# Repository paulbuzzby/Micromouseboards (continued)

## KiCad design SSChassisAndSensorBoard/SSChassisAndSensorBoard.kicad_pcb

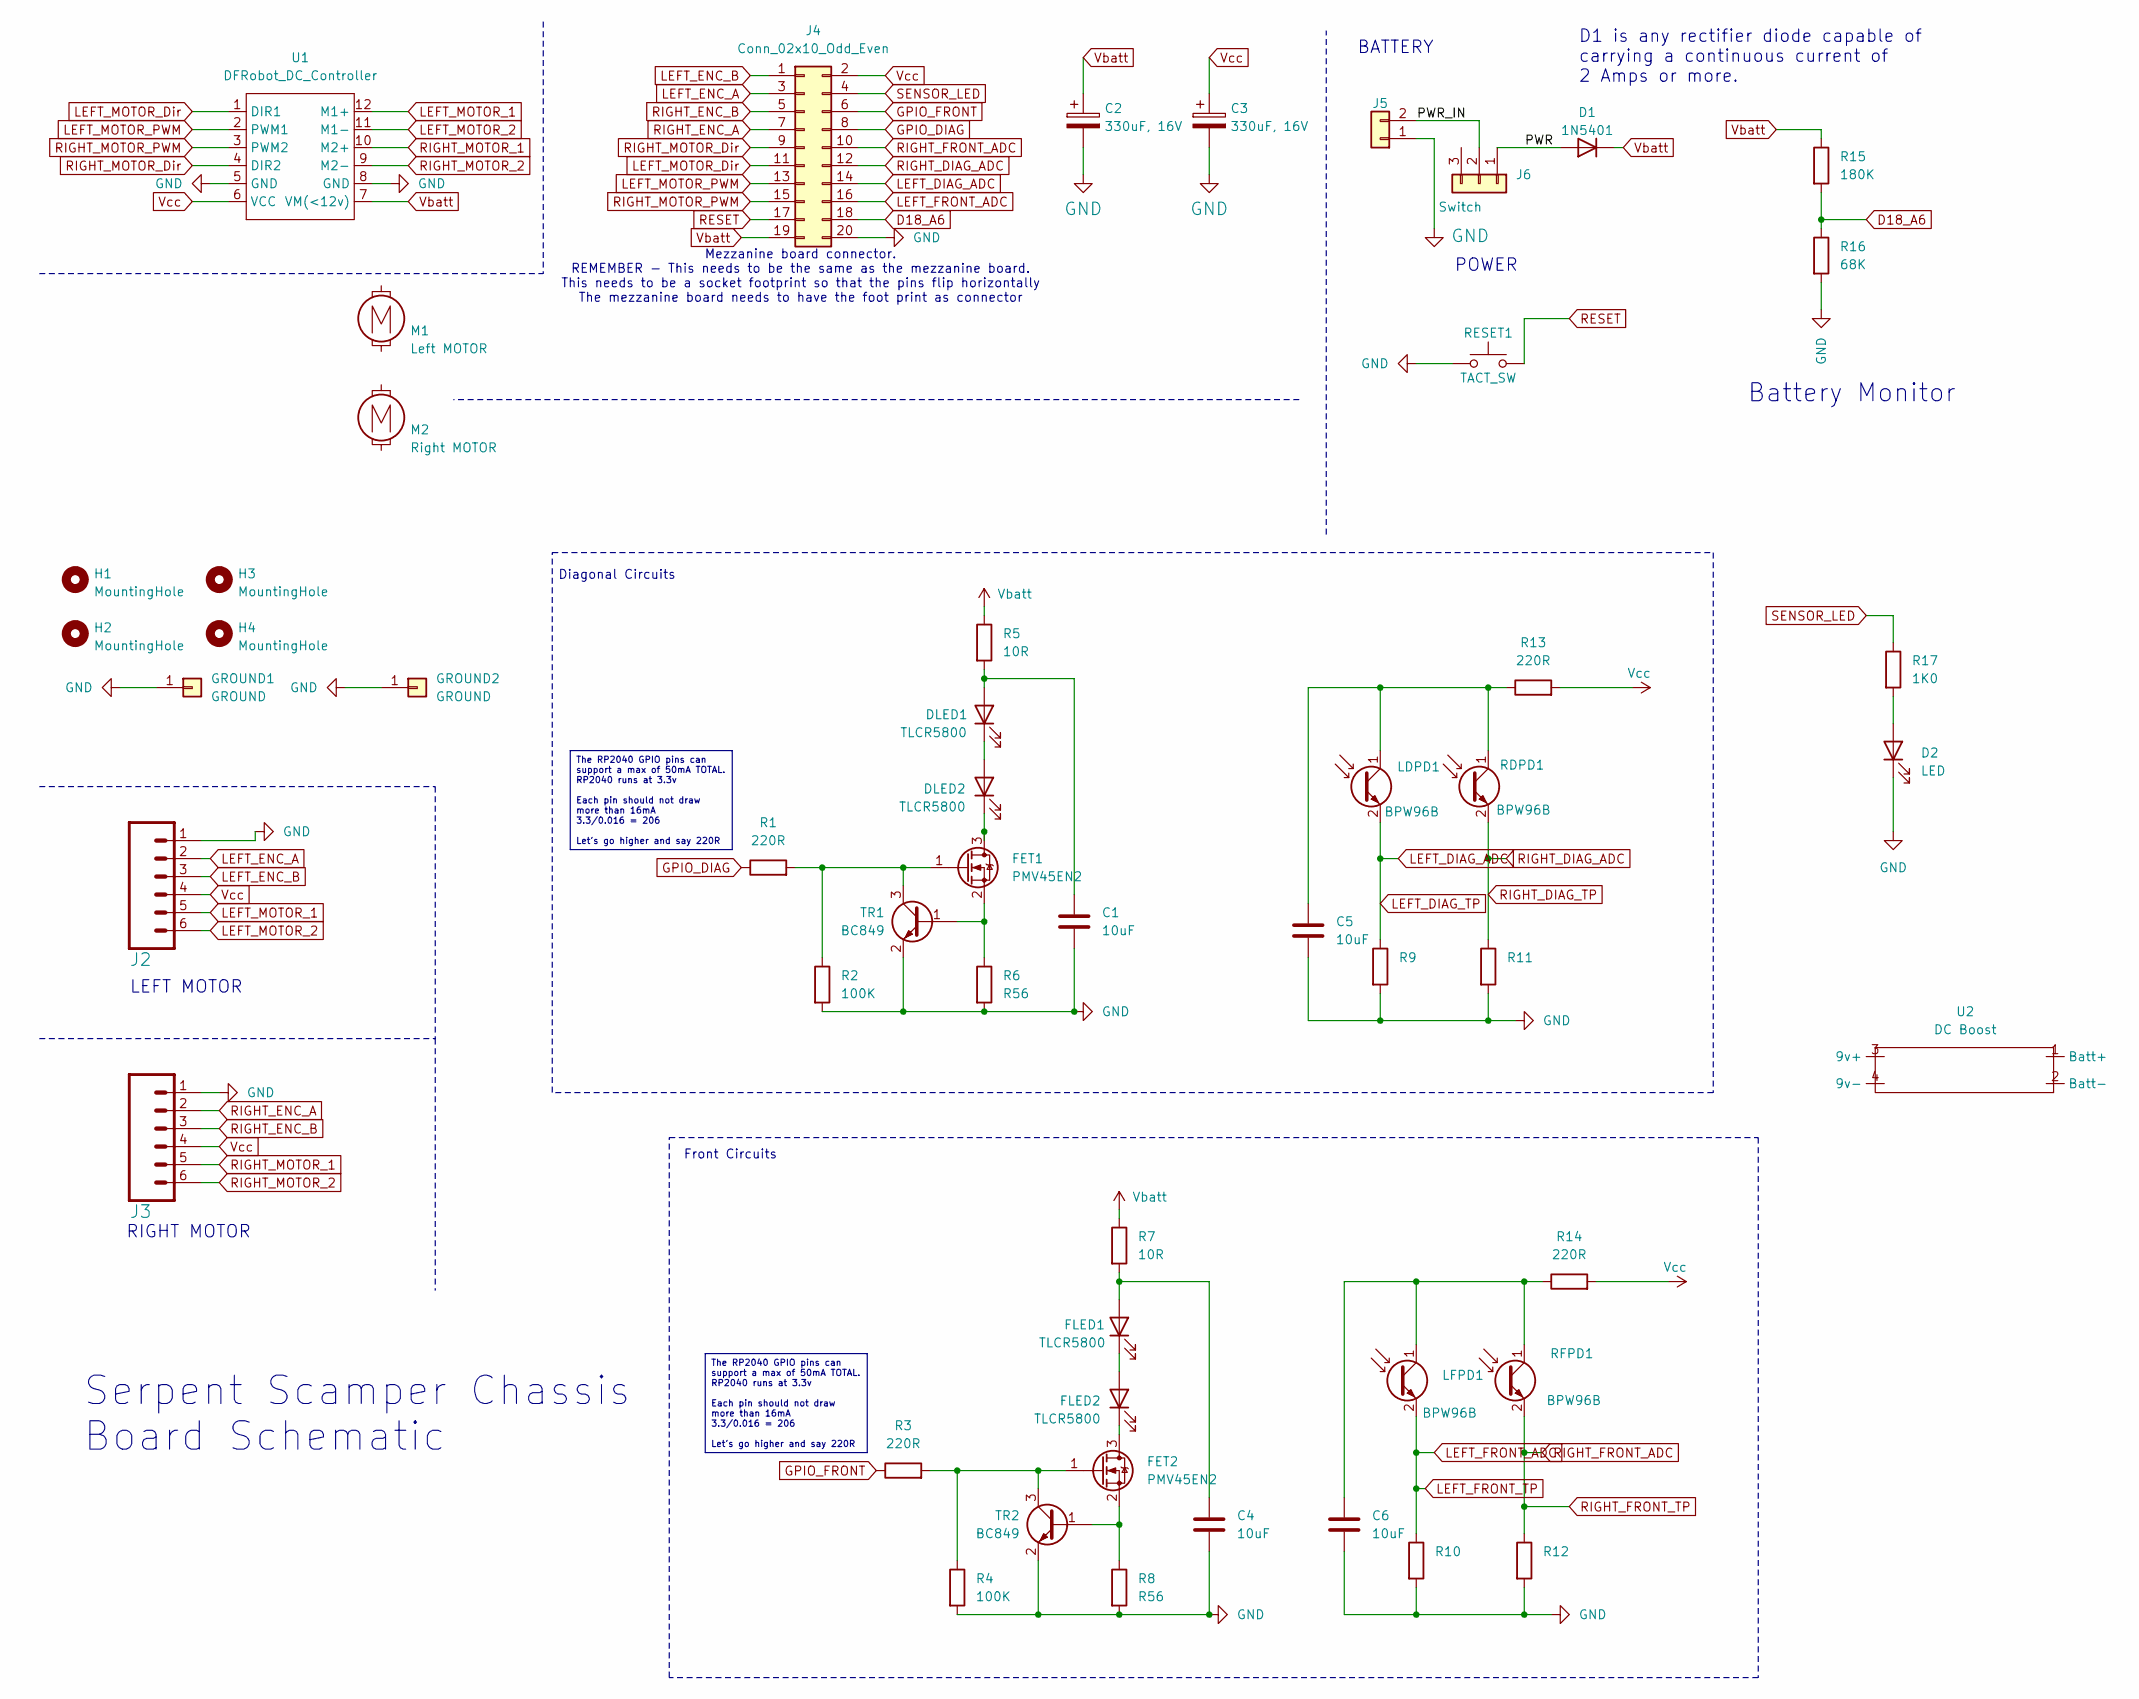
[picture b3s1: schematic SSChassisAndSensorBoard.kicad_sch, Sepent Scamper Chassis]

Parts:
C1, C4, C5, C6: 10uF; C_0805_2012Metric_Pad1.18x1.45mm_HandSolder
C2, C3: 330uF, 16V; CP_Radial_D8.0mm_P2.50mm
D1: 1N5401; D_DO-201AD_P15.24mm_Horizontal
D2: LED; LED_1206_3216Metric_Pad1.42x1.75mm_HandSolder
DLED1, DLED2: TLCR5800; LED_D5.0mm_Horizontal_O1.27mm_Z3.0mm
FET1, FET2: PMV45EN2; SOT-23_Handsoldering
FLED1, FLED2: TLCR5800; LED_D5.0mm_Horizontal_O1.27mm_Z3.0mm
GROUND1, GROUND2: GROUND; PinHeader_1x01_P2.54mm_Vertical
H1, H2, H3, H4: MountingHole; MountingHole_3.2mm_M3_clearance
J2, J3: CONN_06SILK_FEMALE_PTH; 1X06_LOCK_LONGPADS
J4: Conn_02x10_Odd_Even; PinSocket_2x10_P2.54mm_Vertical
J5: POWER; Molex_KK-254_AE-6410-02A_1x02_P2.54mm_Vertical
J6: Switch; PinHeader_1x03_P2.54mm_Vertical
LDPD1: BPW96B; LED_D5.0mm_Horizontal_O1.27mm_Z3.0mm
LFPD1: BPW96B; LED_D5.0mm_Horizontal_O1.27mm_Z3.0mm
M1: Left MOTOR; MINI-METAL-GEARMOTOR-WITH-BRACKET_Alt
M2: Right MOTOR; MINI-METAL-GEARMOTOR-WITH-BRACKET
R1, R3, R13, R14: 220R; R_0805_2012Metric_Pad1.20x1.40mm_HandSolder
R2, R4: 100K; R_0805_2012Metric_Pad1.20x1.40mm_HandSolder
R5, R7: 10R; R_0805_2012Metric_Pad1.20x1.40mm_HandSolder
R6, R8: R56; R_0805_2012Metric_Pad1.20x1.40mm_HandSolder
R9, R10, R11, R12: R; R_0805_2012Metric_Pad1.20x1.40mm_HandSolder
R15: 180K; R_Axial_DIN0207_L6.3mm_D2.5mm_P7.62mm_Horizontal
R16: 68K; R_Axial_DIN0207_L6.3mm_D2.5mm_P7.62mm_Horizontal
R17: 1K0; R_0805_2012Metric_Pad1.20x1.40mm_HandSolder
RDPD1: BPW96B; LED_D5.0mm_Horizontal_O1.27mm_Z3.0mm
RESET1: TACT_SW; SW_PUSH_6mm
RFPD1: BPW96B; LED_D5.0mm_Horizontal_O1.27mm_Z3.0mm
TR1, TR2: BC849; SOT-23_Handsoldering
U1: DFRobot_DC_Controller
U2: DC Boost

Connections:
/PWR: D1.2 (A), J6.1
/PWR_IN: J5.2, J6.2
D18_A6: J4.18, R15.2, R16.1
GND: C1.2, C2.2, C3.2, C4.2, C5.2, C6.2, D2.1 (K), GROUND1.1, GROUND2.1, J2.1, J3.1, J4.20, J5.1, R2.2, R4.2, R6.2, R8.2, R9.2, R10.2, R11.2, R12.2, R16.2, RESET1.1 (A), TR1.2 (E), TR2.2 (E), U1.5 (GND), U1.8 (GND)
GPIO_DIAG: J4.8, R1.1
GPIO_FRONT: J4.6, R3.1
LEFT_DIAG_ADC: J4.14, LDPD1.2 (E), R9.1
LEFT_ENC_A: J2.2, J4.3
LEFT_ENC_B: J2.3, J4.1
LEFT_FRONT_ADC: J4.16, LFPD1.2 (E), R10.1
LEFT_MOTOR_1: J2.5, U1.12 (M1+)
LEFT_MOTOR_2: J2.6, U1.11 (M1-)
LEFT_MOTOR_Dir: J4.11, U1.1 (DIR1)
LEFT_MOTOR_PWM: J4.13, U1.2 (PWM1)
unnamed: D2.2 (A), R17.2
unnamed: C1.1, DLED1.2 (A), R5.2
unnamed: DLED1.1 (K), DLED2.2 (A)
unnamed: DLED2.1 (K), FET1.3 (D)
unnamed: FET1.1 (G), R1.2, R2.1, TR1.3 (C)
unnamed: FET1.2 (S), R6.1, TR1.1 (B)
unnamed: FET2.3 (D), FLED2.1 (K)
unnamed: FET2.1 (G), R3.2, R4.1, TR2.3 (C)
unnamed: FET2.2 (S), R8.1, TR2.1 (B)
unnamed: C4.1, FLED1.2 (A), R7.2
unnamed: FLED1.1 (K), FLED2.2 (A)
unnamed: C5.1, LDPD1.1 (C), R13.1, RDPD1.1 (C)
unnamed: C6.1, LFPD1.1 (C), R14.1, RFPD1.1 (C)
RESET: J4.17, RESET1.2 (B)
RIGHT_DIAG_ADC: J4.12, R11.1, RDPD1.2 (E)
RIGHT_ENC_A: J3.2, J4.7
RIGHT_ENC_B: J3.3, J4.5
RIGHT_FRONT_ADC: J4.10, R12.1, RFPD1.2 (E)
RIGHT_MOTOR_1: J3.5, U1.10 (M2+)
RIGHT_MOTOR_2: J3.6, U1.9 (M2-)
RIGHT_MOTOR_Dir: J4.9, U1.4 (DIR2)
RIGHT_MOTOR_PWM: J4.15, U1.3 (PWM2)
SENSOR_LED: J4.4, R17.1
Vbatt: C2.1, D1.1 (K), J4.19, R5.1, R7.1, R15.1, U1.7 (VM(<12v))
Vcc: C3.1, J2.4, J3.4, J4.2, R13.2, R14.2, U1.6 (VCC)

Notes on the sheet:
The RP2040 GPIO pins can support a max of 50mA TOTAL. RP2040 runs at 3.3v Each pin should not draw more than 16mA 3.3/0.016 = 206 Let's go higher and say 220R
D1 is any rectifier diode capable of carrying a continuous current of 2 Amps or more.
Front Circuits
POWER
Diagonal Circuits
RIGHT MOTOR
BATTERY
Mezzanine board connector. REMEMBER - This needs to be the same as the mezzanine board. This needs to be a socket footprint so that the pins flip horizontally The mezzanine board needs to have the foot print as connector
Serpent Scamper Chassis Board Schematic
LEFT MOTOR
Battery Monitor

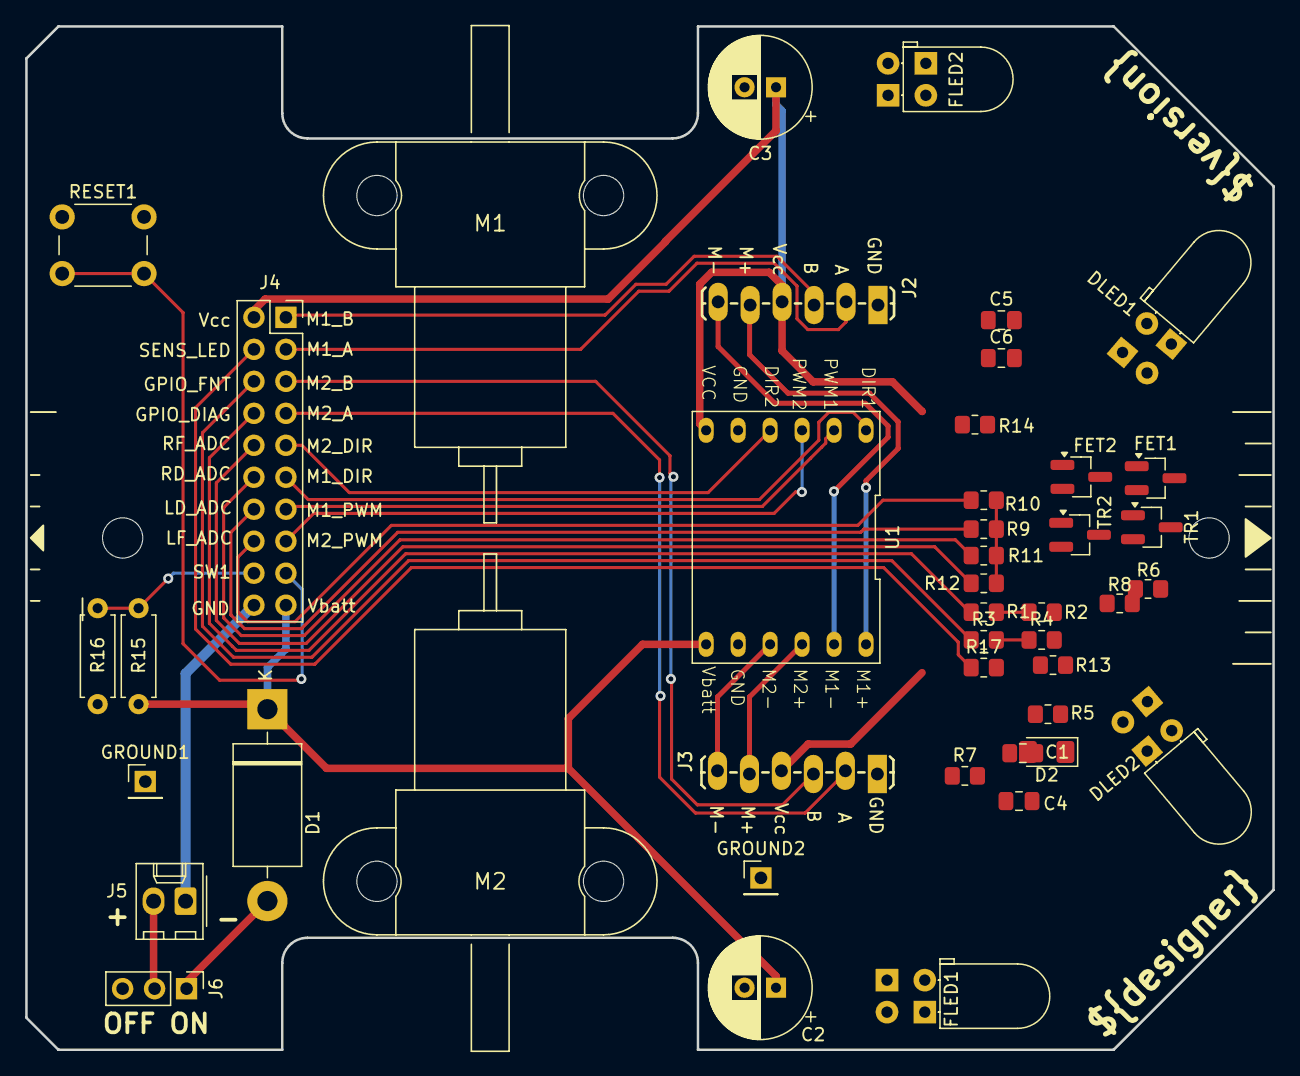
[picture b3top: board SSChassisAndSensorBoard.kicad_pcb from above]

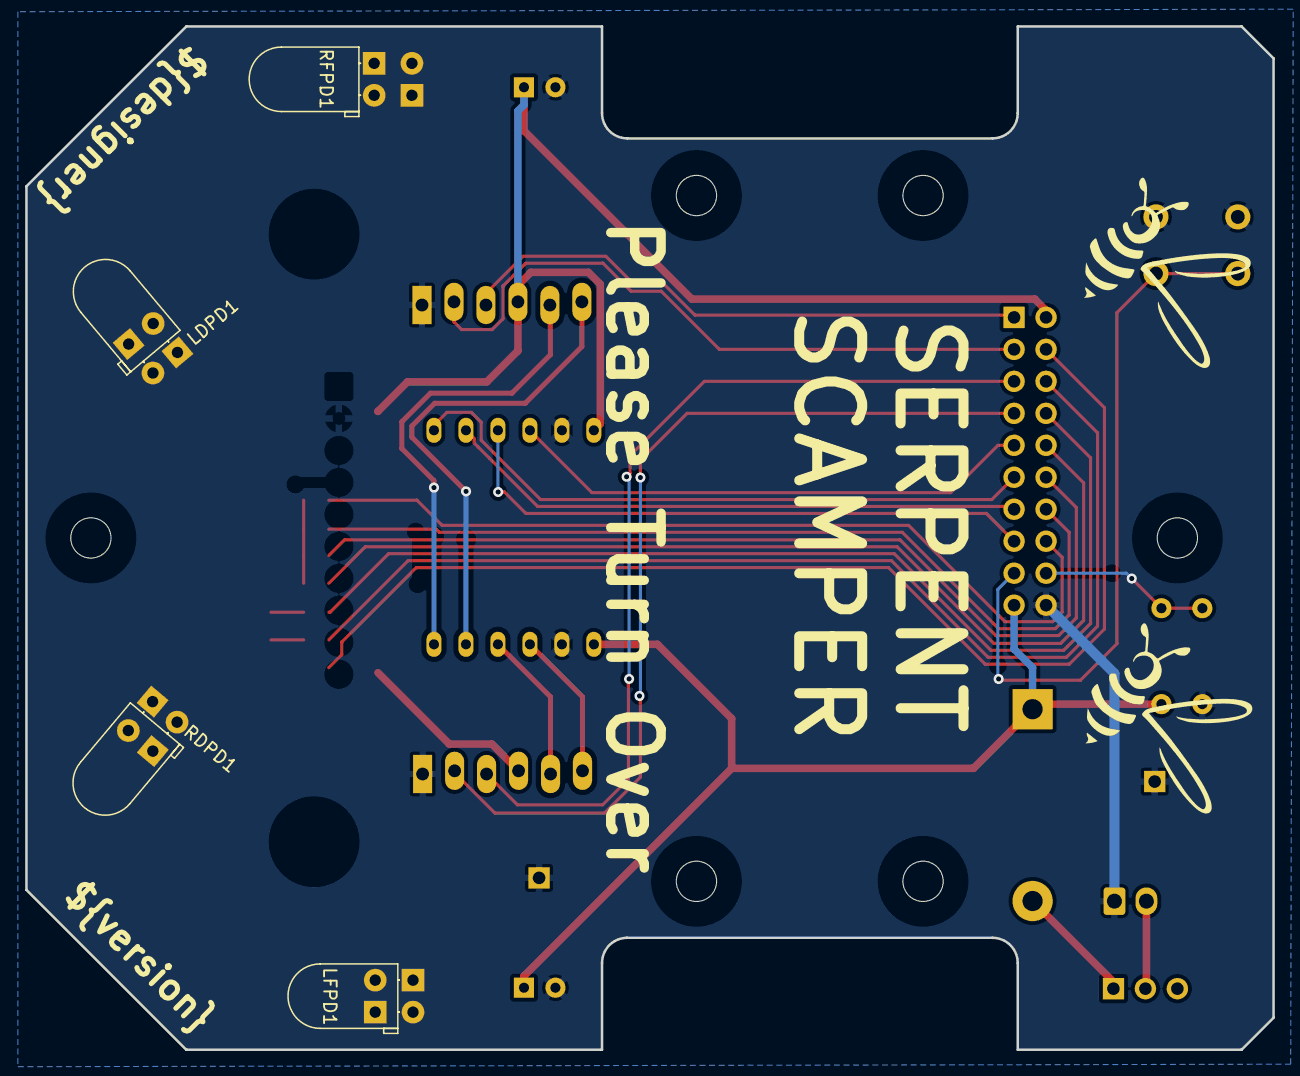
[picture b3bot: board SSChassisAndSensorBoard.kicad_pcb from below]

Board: 2 copper layers, 99.1 x 81.3 mm, 52 parts (4 on the bottom side), 39 nets.

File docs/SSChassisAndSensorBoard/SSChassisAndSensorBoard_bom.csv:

Reference,Value,Qty,Note,Description
C1 C4 C5 C6,10uF,4,,Unpolarized capacitor
C2 C3,"330uF, 16V",2,Maximum height is 10mm,
D1,1N5401,1,> 2A rectifier. Shottky is good,
D2,LED,1,,Light emitting diode
DLED1 DLED2 FLED1 FLED2,TLCR5800,4,,Light emitting diode
FET1 FET2,PMV45EN2,2,,"N-Channel MOSFET, 5.1 A, 30 V, 3-Pin SOT-23"
GROUND1 GROUND2 J4 J5 J6,GROUND,5,"0.1"" pitch, polarised, any type","Generic connector, single row, 01x01, script generated (kicad-library-utils/schlib/autogen/connector/) Generic connector, double row, 02x10, odd/even pin numbering scheme (row 1 odd numbers, row 2 even numbers), script generated (kicad-library-utils/schlib/autogen/connector/) Generic connector, single row, 01x03, script generated (kicad-library-utils/schlib/autogen/connector/)"
J2 J3,CONN_06SILK_FEMALE_PTH,2,"6 pin header, 0.1"", male",
LDPD1 LFPD1 RDPD1 RFPD1,BPW96B,4,,Photodiode
M1,Left MOTOR,1,commercial mounts need bushing for screws,
M2,Right MOTOR,1,commercial mounts need bushing for screws,
R2 R4,100K,2,,Resistor
R5 R7,10R,2,,Resistor
R15,180K,1,,Resistor
R17,1K0,1,,Resistor
R1 R3 R13 R14,220R,4,,Resistor
R16,68K,1,,Resistor
R9 R10 R11 R12,R,4,,Resistor
R6 R8,R56,2,,Resistor
RESET1,TACT_SW,1,,TACT switch 6mm 4.5mm
TR1 TR2,BC849,2,,"0.1A Ic, 30V Vce, NPN Transistor, SOT-23"
U2,DC Boost,1,,DC-DC boost converter
U1,DFRobot_DC_Controller,1,,

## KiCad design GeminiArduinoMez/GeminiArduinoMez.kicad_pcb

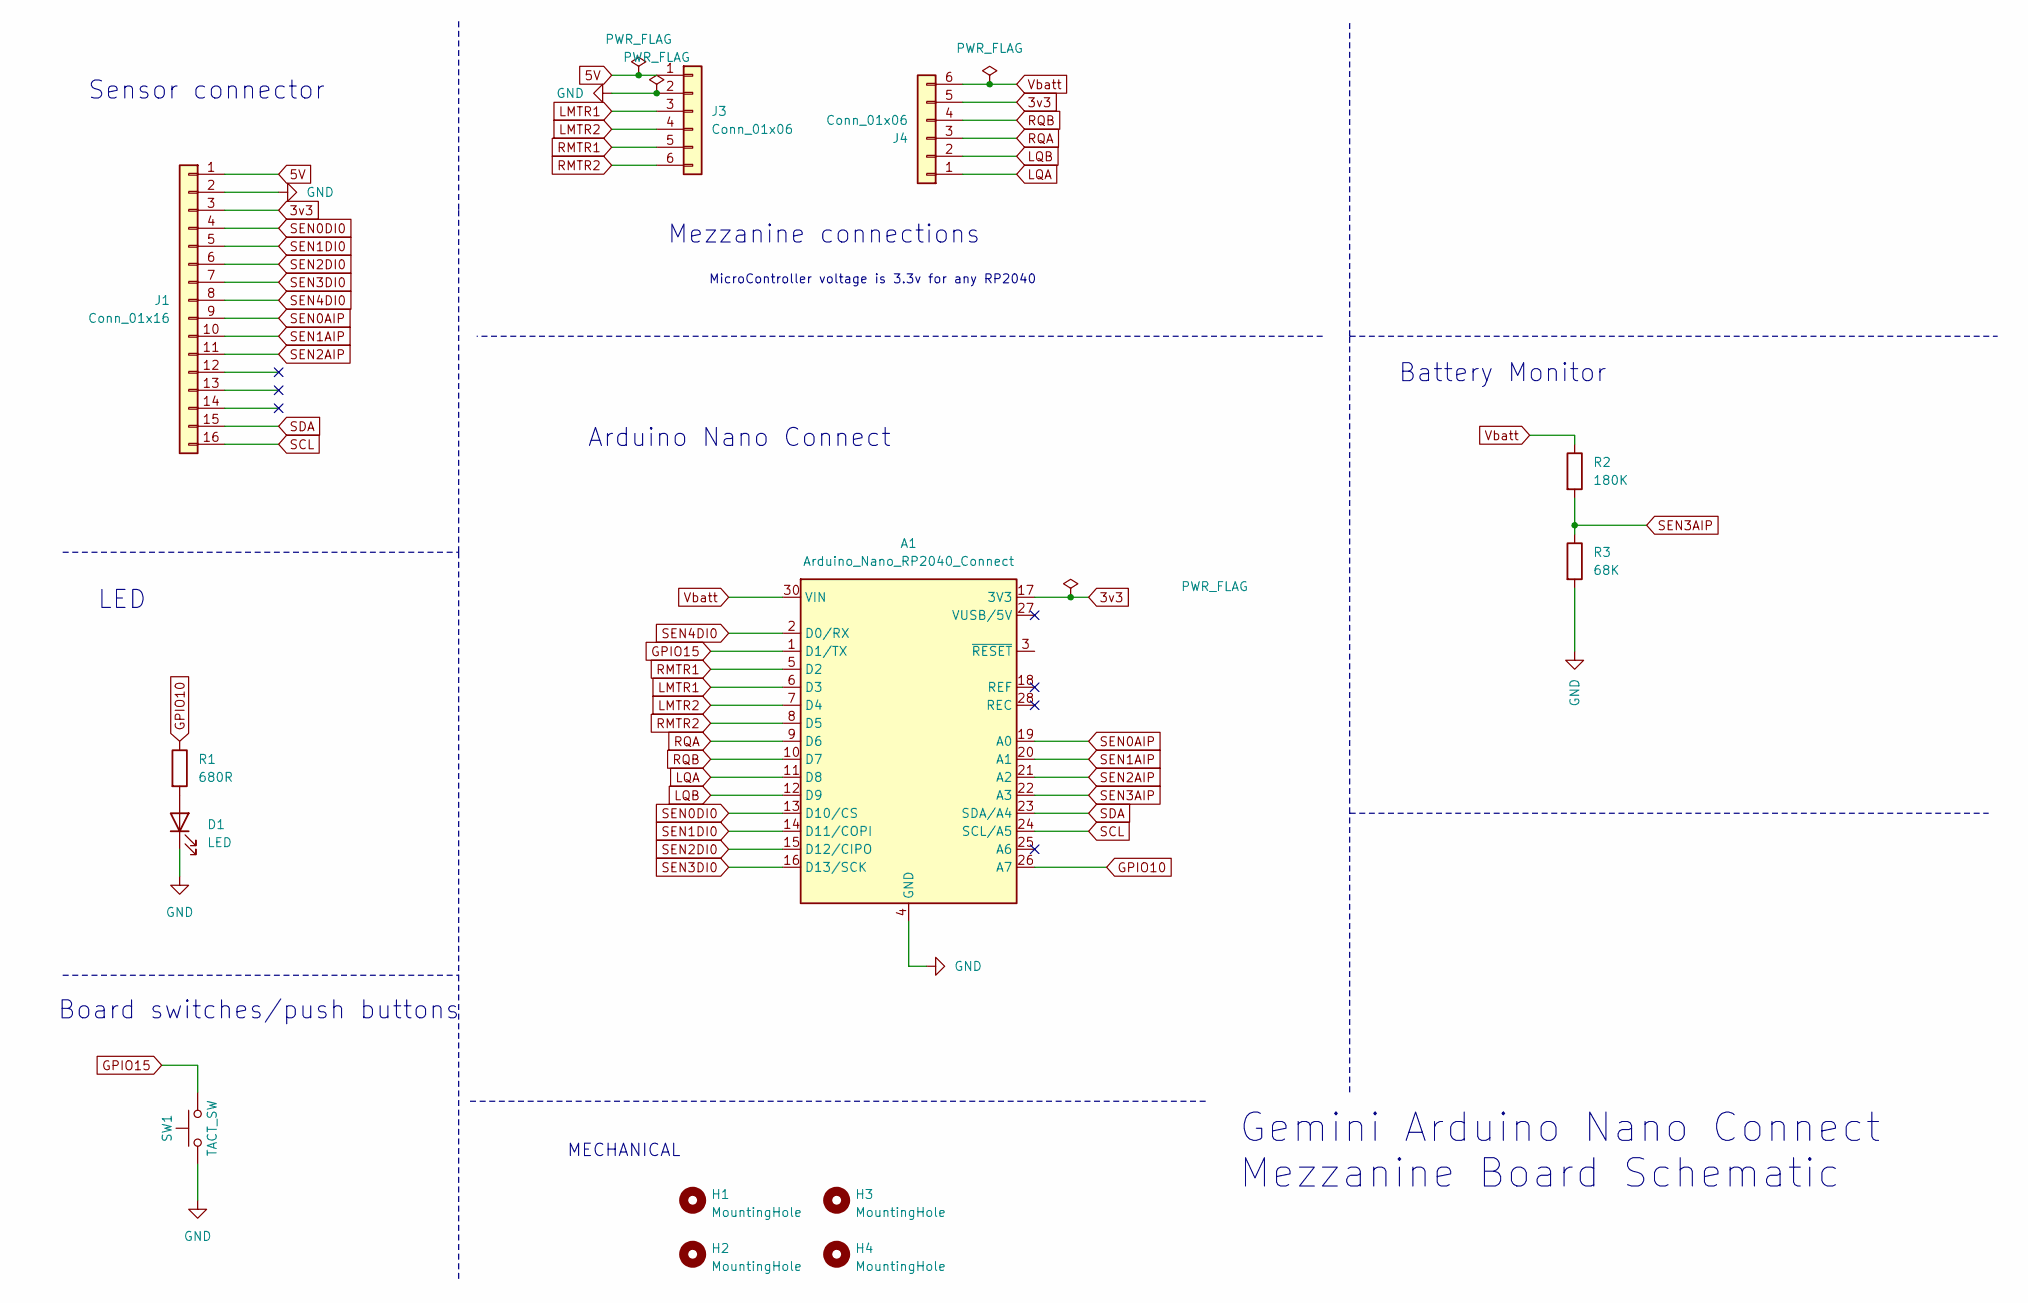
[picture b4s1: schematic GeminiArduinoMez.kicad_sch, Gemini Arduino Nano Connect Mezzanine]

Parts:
A1: Arduino_Nano_RP2040_Connect; Arduino_Nano
D1: LED; LED_D5.0mm
H1, H2, H3, H4: MountingHole; MountingHole_3.2mm_M3_clearance
J1: Conn_01x16; PinHeader_1x16_P2.54mm_Vertical
J3, J4: Conn_01x06; PinHeader_1x06_P2.54mm_Vertical
R1: 680R; R_Axial_DIN0207_L6.3mm_D2.5mm_P7.62mm_Horizontal
R2: 180K; R_Axial_DIN0207_L6.3mm_D2.5mm_P7.62mm_Horizontal
R3: 68K; R_Axial_DIN0207_L6.3mm_D2.5mm_P7.62mm_Horizontal
SW1: TACT_SW; SW_PUSH_6mm

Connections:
3v3: A1.17 (3V3), J1.3, J4.5
5V: J1.1, J3.1
GND: A1.4 (GND), A1.29 (GND), D1.1 (K), J1.2, J3.2, R3.2, SW1.1 (A)
GPIO10: A1.26 (A7), R1.1
GPIO15: A1.1 (D1/TX), SW1.2 (B)
LMTR1: A1.6 (D3), J3.3
LMTR2: A1.7 (D4), J3.4
LQA: A1.11 (D8), J4.1
LQB: A1.12 (D9), J4.2
unnamed: D1.2 (A), R1.2
RMTR1: A1.5 (D2), J3.5
RMTR2: A1.8 (D5), J3.6
RQA: A1.9 (D6), J4.3
RQB: A1.10 (D7), J4.4
SCL: A1.24 (SCL/A5), J1.16
SDA: A1.23 (SDA/A4), J1.15
SEN0AIP: A1.19 (A0), J1.9
SEN0DI0: A1.13 (D10/CS), J1.4
SEN1AIP: A1.20 (A1), J1.10
SEN1DI0: A1.14 (D11/COPI), J1.5
SEN2AIP: A1.21 (A2), J1.11
SEN2DI0: A1.15 (D12/CIPO), J1.6
SEN3AIP: A1.22 (A3), R2.2, R3.1
SEN3DI0: A1.16 (D13/SCK), J1.7
SEN4DI0: A1.2 (D0/RX), J1.8
Vbatt: A1.30 (VIN), J4.6, R2.1

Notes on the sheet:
Board switches/push buttons
MicroController voltage is 3.3v for any RP2040
LED
Sensor connector
MECHANICAL
Arduino Nano Connect
Mezzanine connections
Gemini Arduino Nano Connect Mezzanine Board Schematic
Battery Monitor

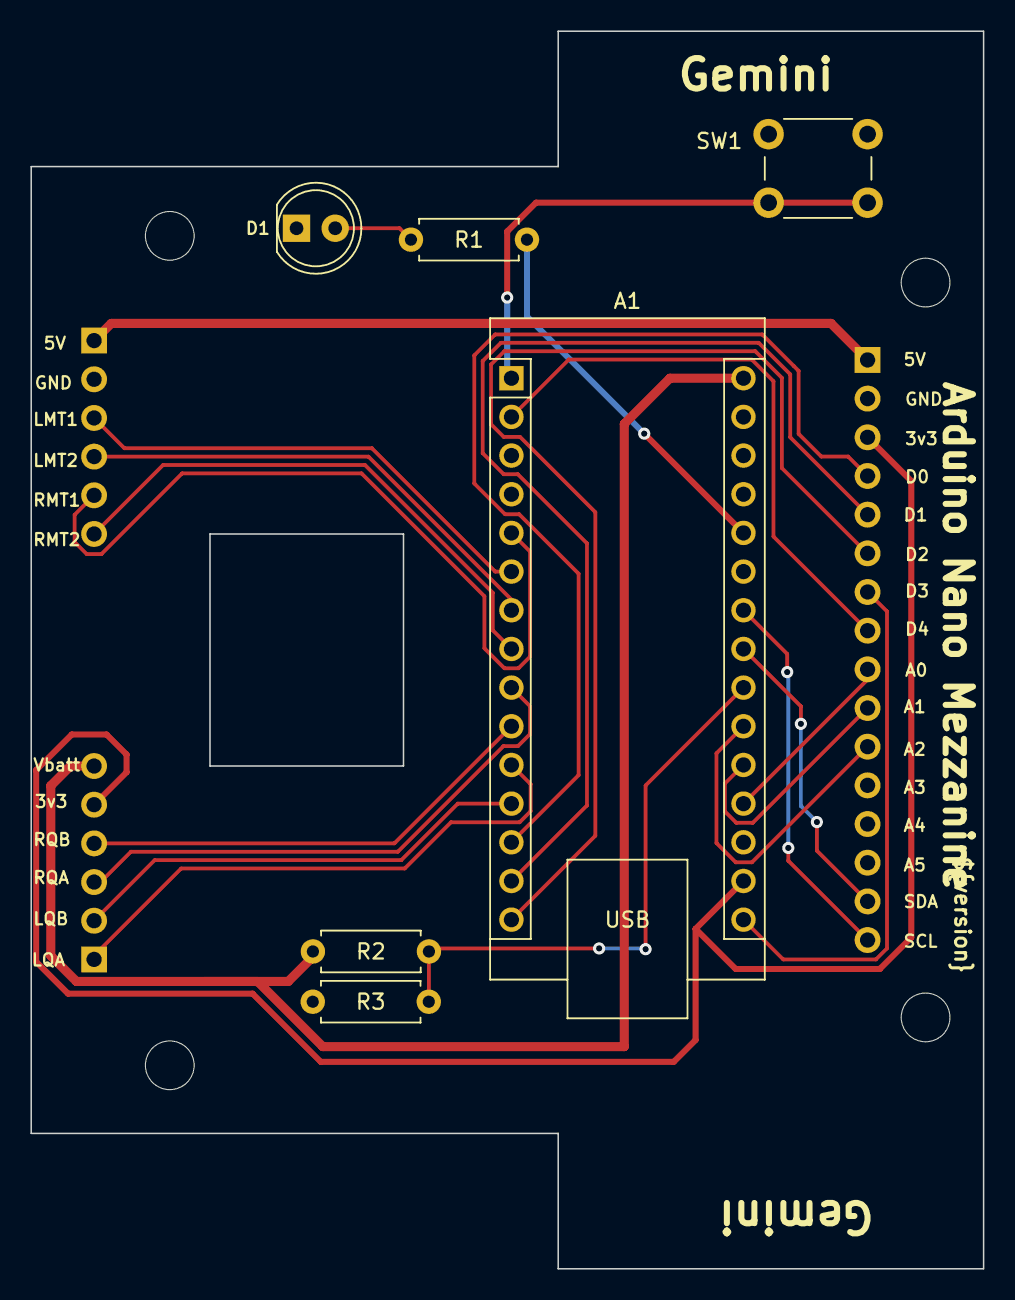
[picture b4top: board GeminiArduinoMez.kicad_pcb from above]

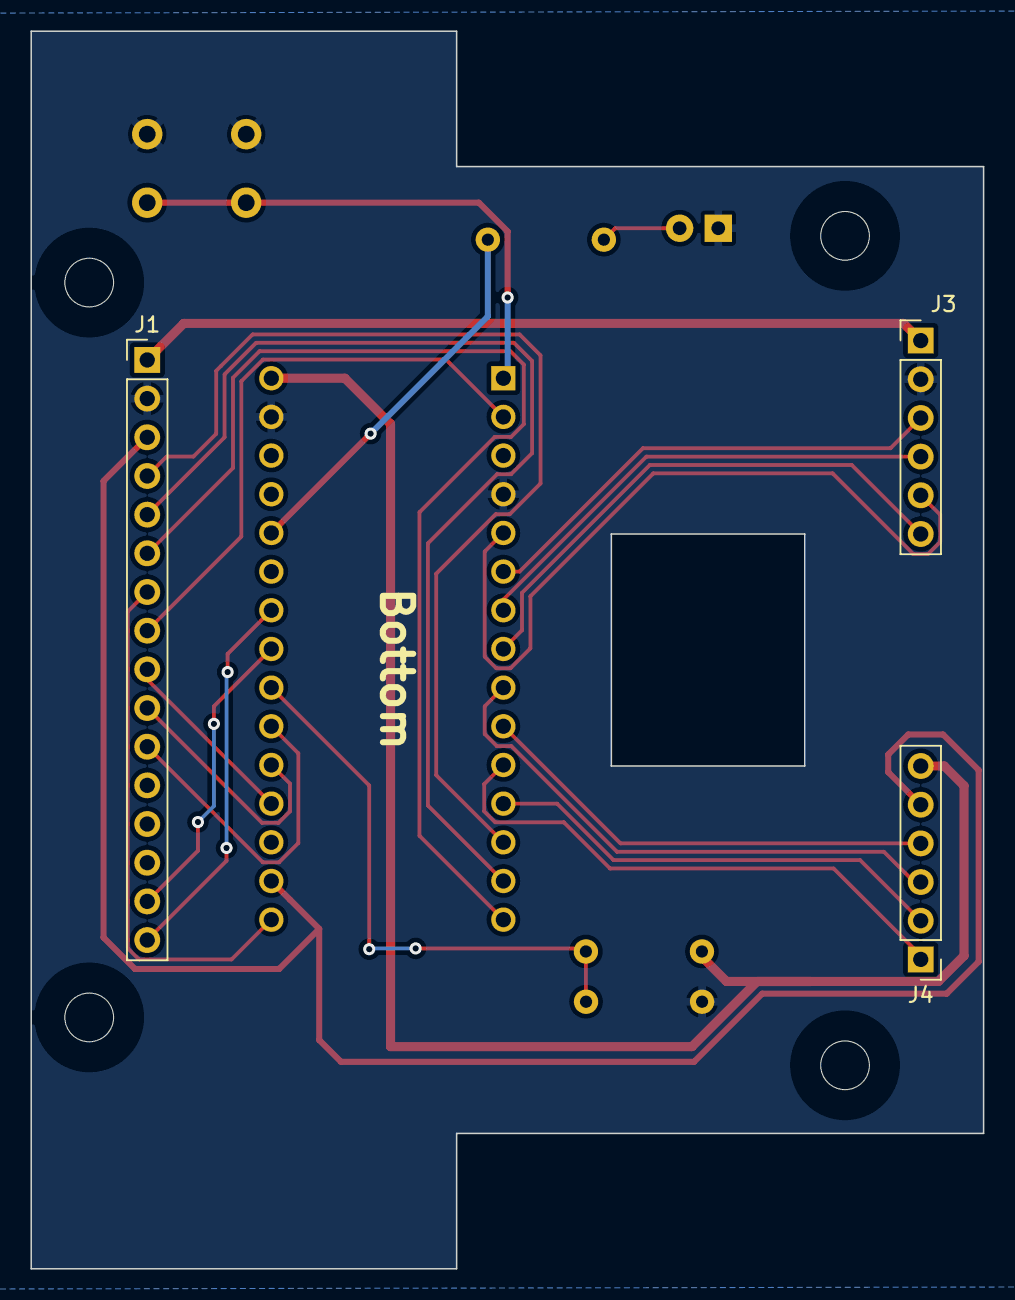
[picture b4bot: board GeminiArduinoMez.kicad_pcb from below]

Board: 2 copper layers, 62.5 x 81.3 mm, 13 parts (3 on the bottom side), 26 nets.

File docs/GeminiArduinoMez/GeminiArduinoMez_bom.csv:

Reference,Value,Qty,Note,Description
A1,Arduino_Nano_RP2040_Connect,1,,"Arduino Nano board based on the RP2040 microcontroller with a dual-core 133 MHz ARM Cortex-M0+ processor, 264 kB SRAM, and up to 16 MB flash memory. Operates at 3.3V, with 5V Micro USB input and 4-20V VIN. Features Wi-Fi®, Bluetooth® LE, digital and analog pins, and supports SPI, I2C, UART, and PIO. Includes a 6-axis IMU, RGB LED, microphone, and cryptographic chip for secure communication."
D1,LED,1,,Light emitting diode
J1 J3 J4,Conn_01x16,3,,"Generic connector, single row, 01x16, script generated (kicad-library-utils/schlib/autogen/connector/) Generic connector, single row, 01x06, script generated (kicad-library-utils/schlib/autogen/connector/)"
R2,180K,1,,Resistor
R1,680R,1,,Resistor
R3,68K,1,,Resistor
SW1,TACT_SW,1,,TACT switch 6mm 4.5mm

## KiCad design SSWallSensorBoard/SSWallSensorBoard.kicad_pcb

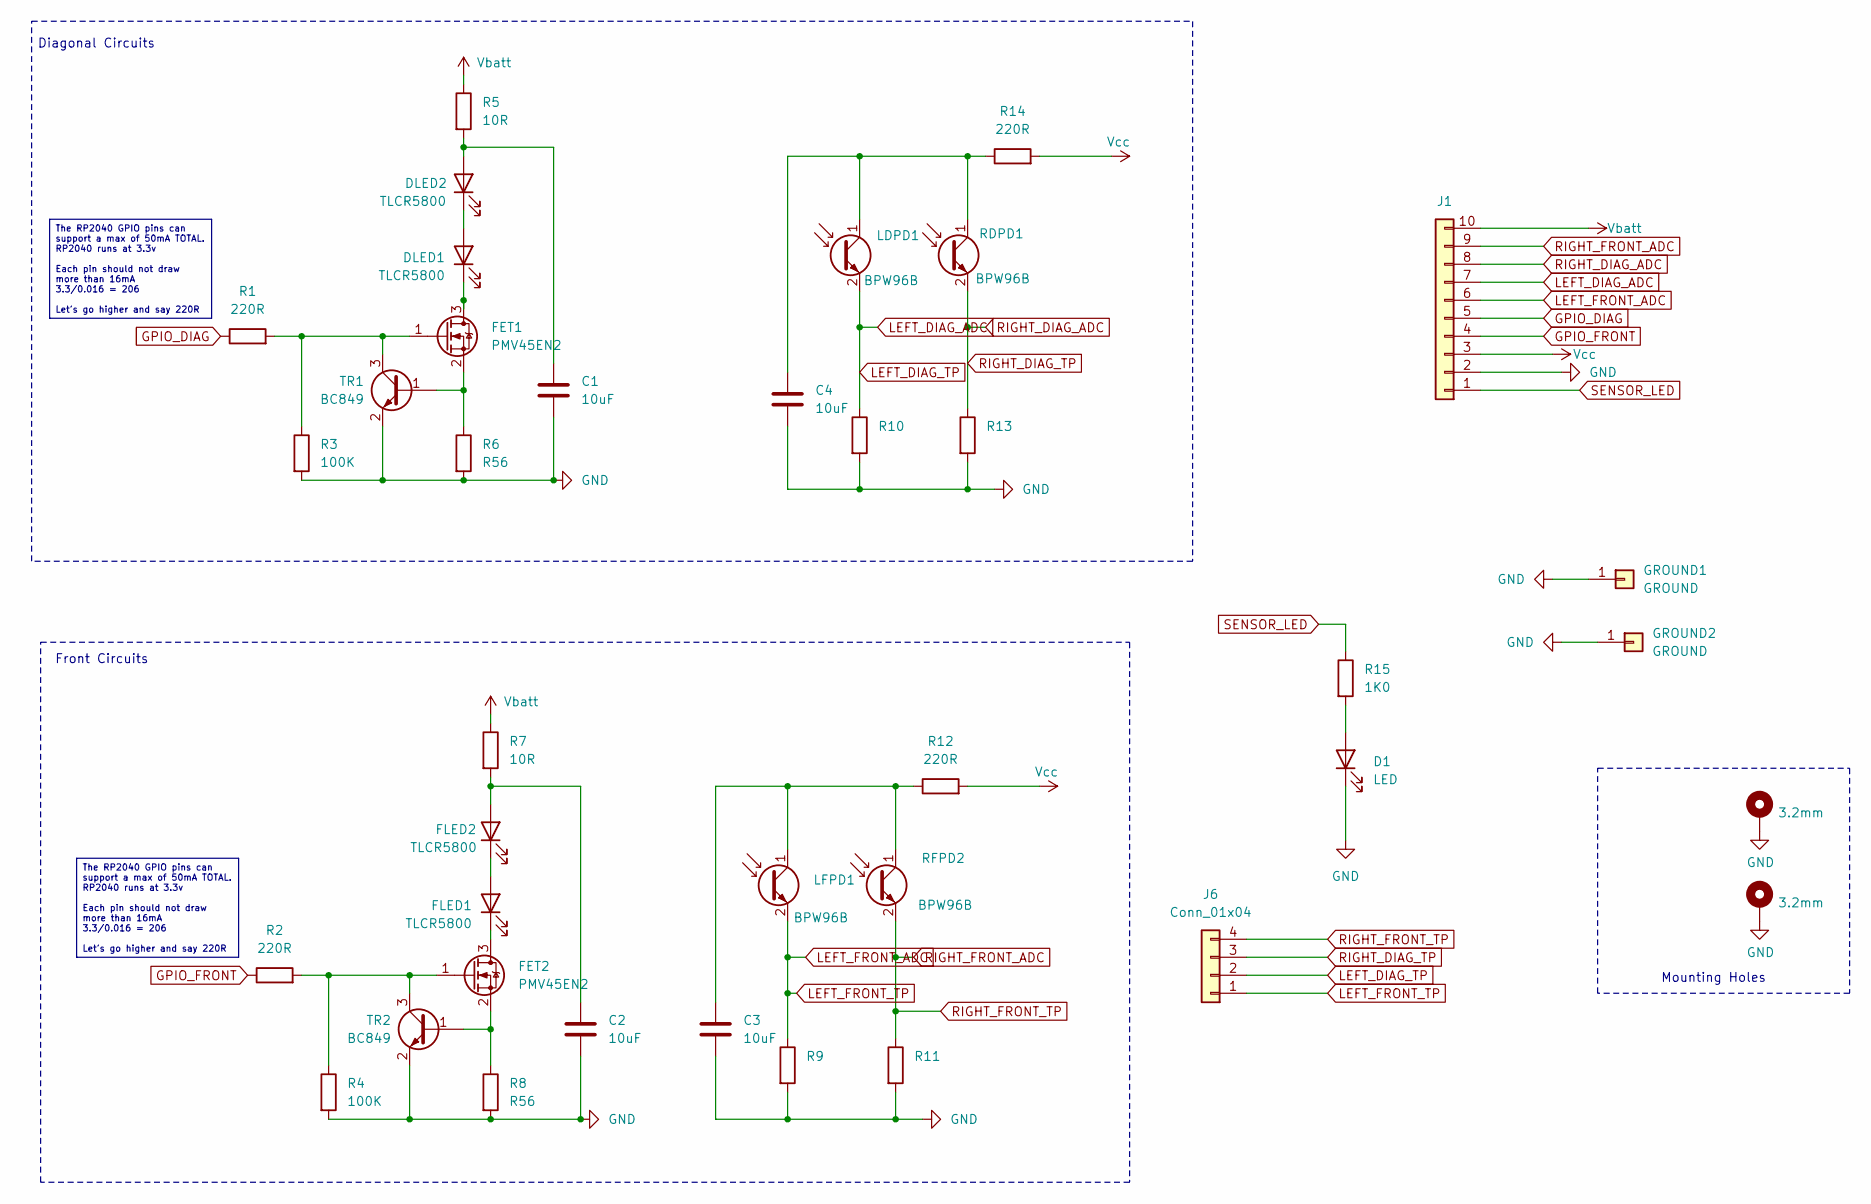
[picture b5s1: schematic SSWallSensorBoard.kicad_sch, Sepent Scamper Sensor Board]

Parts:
C1, C2, C3, C4: 10uF; C_0805_2012Metric_Pad1.18x1.45mm_HandSolder
D1: LED; LED_1206_3216Metric_Pad1.42x1.75mm_HandSolder
DLED1, DLED2: TLCR5800; LED_D5.0mm_Horizontal_O1.27mm_Z3.0mm
FET1, FET2: PMV45EN2; SOT-23_Handsoldering
FLED1, FLED2: TLCR5800; LED_D5.0mm_Horizontal_O1.27mm_Z3.0mm
GROUND1, GROUND2: GROUND; PinHeader_1x01_P2.54mm_Vertical
H1, H2: 3.2mm; MountingHole_3.2mm_M3_Pad
J1: Conn_01x10; PinHeader_1x10_P2.54mm_Vertical
J6: Conn_01x04; PinHeader_1x04_P2.54mm_Vertical
LDPD1: BPW96B; LED_D5.0mm_Horizontal_O1.27mm_Z3.0mm
LFPD1: BPW96B; LED_D5.0mm_Horizontal_O1.27mm_Z3.0mm
R1, R2, R12, R14: 220R; R_0805_2012Metric_Pad1.20x1.40mm_HandSolder
R3, R4: 100K; R_0805_2012Metric_Pad1.20x1.40mm_HandSolder
R5, R7: 10R; R_0805_2012Metric_Pad1.20x1.40mm_HandSolder
R6, R8: R56; R_0805_2012Metric_Pad1.20x1.40mm_HandSolder
R9, R10, R11, R13: R; R_0805_2012Metric_Pad1.20x1.40mm_HandSolder
R15: 1K0; R_0805_2012Metric_Pad1.20x1.40mm_HandSolder
RDPD1: BPW96B; LED_D5.0mm_Horizontal_O1.27mm_Z3.0mm
RFPD2: BPW96B; LED_D5.0mm_Horizontal_O1.27mm_Z3.0mm
TR1, TR2: BC849; SOT-23_Handsoldering

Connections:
GND: C1.2, C2.2, C3.2, C4.2, D1.1 (K), GROUND1.1, GROUND2.1, H1.1, H2.1, J1.2, R3.2, R4.2, R6.2, R8.2, R9.2, R10.2, R11.2, R13.2, TR1.2 (E), TR2.2 (E)
GPIO_DIAG: J1.5, R1.1
GPIO_FRONT: J1.4, R2.1
LEFT_DIAG_ADC: J1.7, J6.2, LDPD1.2 (E), R10.1
LEFT_FRONT_ADC: J1.6, J6.1, LFPD1.2 (E), R9.1
unnamed: D1.2 (A), R15.2
unnamed: DLED1.2 (A), DLED2.1 (K)
unnamed: DLED1.1 (K), FET1.3 (D)
unnamed: C1.1, DLED2.2 (A), R5.2
unnamed: FET1.1 (G), R1.2, R3.1, TR1.3 (C)
unnamed: FET1.2 (S), R6.1, TR1.1 (B)
unnamed: FET2.3 (D), FLED1.1 (K)
unnamed: FET2.1 (G), R2.2, R4.1, TR2.3 (C)
unnamed: FET2.2 (S), R8.1, TR2.1 (B)
unnamed: FLED1.2 (A), FLED2.1 (K)
unnamed: C2.1, FLED2.2 (A), R7.2
unnamed: C4.1, LDPD1.1 (C), R14.1, RDPD1.1 (C)
unnamed: C3.1, LFPD1.1 (C), R12.1, RFPD2.1 (C)
RIGHT_DIAG_ADC: J1.8, J6.3, R13.1, RDPD1.2 (E)
RIGHT_FRONT_ADC: J1.9, J6.4, R11.1, RFPD2.2 (E)
SENSOR_LED: J1.1, R15.1
Vbatt: J1.10, R5.1, R7.1
Vcc: J1.3, R12.2, R14.2

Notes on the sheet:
The RP2040 GPIO pins can support a max of 50mA TOTAL. RP2040 runs at 3.3v Each pin should not draw more than 16mA 3.3/0.016 = 206 Let's go higher and say 220R
Diagonal Circuits
Mounting Holes
Front Circuits

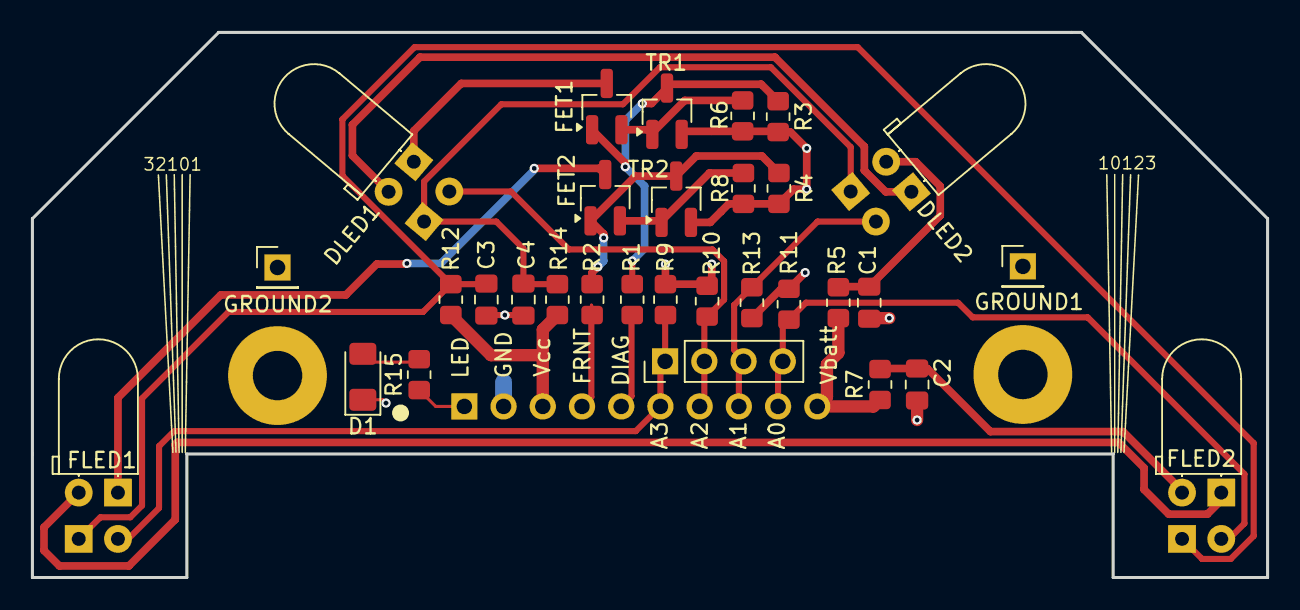
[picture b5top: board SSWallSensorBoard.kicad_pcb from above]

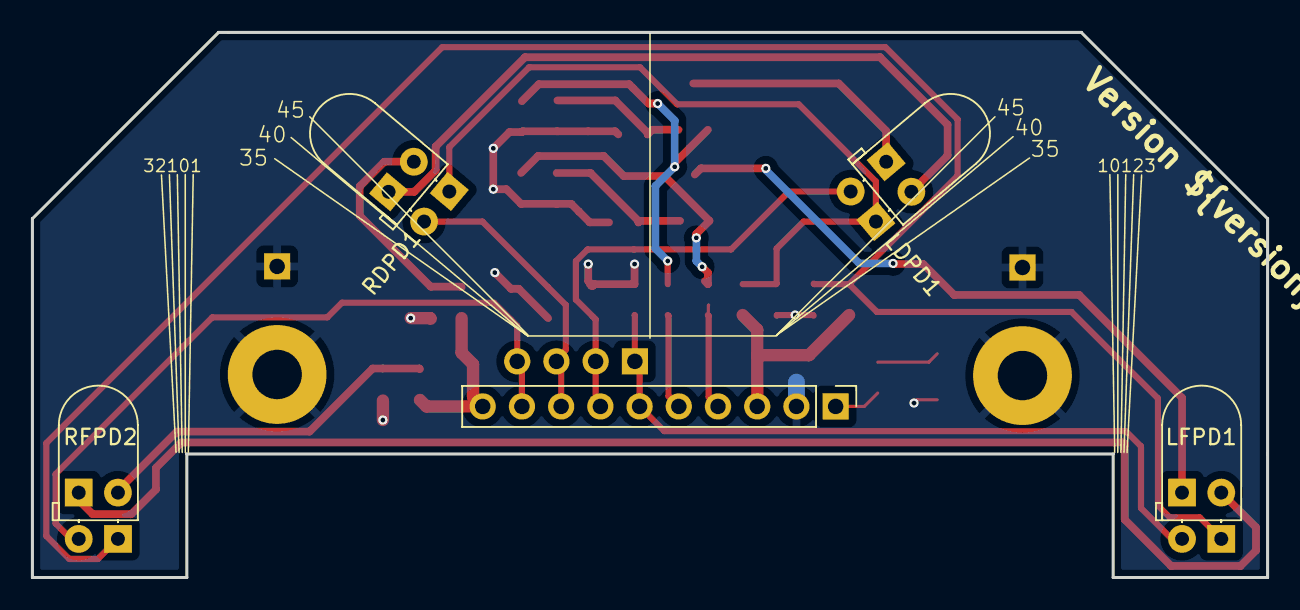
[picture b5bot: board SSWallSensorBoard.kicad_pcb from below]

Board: 2 copper layers, 80.0 x 35.3 mm, 38 parts (5 on the bottom side), 23 nets.

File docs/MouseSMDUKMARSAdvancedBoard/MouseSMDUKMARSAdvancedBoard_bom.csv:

Reference,Value,Qty,Note,Description
C1 C2 C3 C4,10uF,4,,Unpolarized capacitor
D1,LED,1,,Light emitting diode
DLED1 DLED2 FLED1 FLED2,TLCR5800,4,,Light emitting diode
FET1 FET2,PMV45EN2,2,,"N-Channel MOSFET, 5.1 A, 30 V, 3-Pin SOT-23"
J1,Conn_01x10,1,,"Generic connector, single row, 01x10, script generated (kicad-library-utils/schlib/autogen/connector/)"
LDPD1 LFPD1 RDPD1 RFPD2,BPW96B,4,,Photodiode
R3 R4,100K,2,,Resistor
R5 R7,10R,2,,Resistor
R15,1K0,1,,Resistor
R1 R2 R12 R14,220R,4,,Resistor
R9 R10 R11 R13,R,4,,Resistor
R6 R8,R56,2,,Resistor
TR1 TR2,BC849,2,,"0.1A Ic, 30V Vce, NPN Transistor, SOT-23"
